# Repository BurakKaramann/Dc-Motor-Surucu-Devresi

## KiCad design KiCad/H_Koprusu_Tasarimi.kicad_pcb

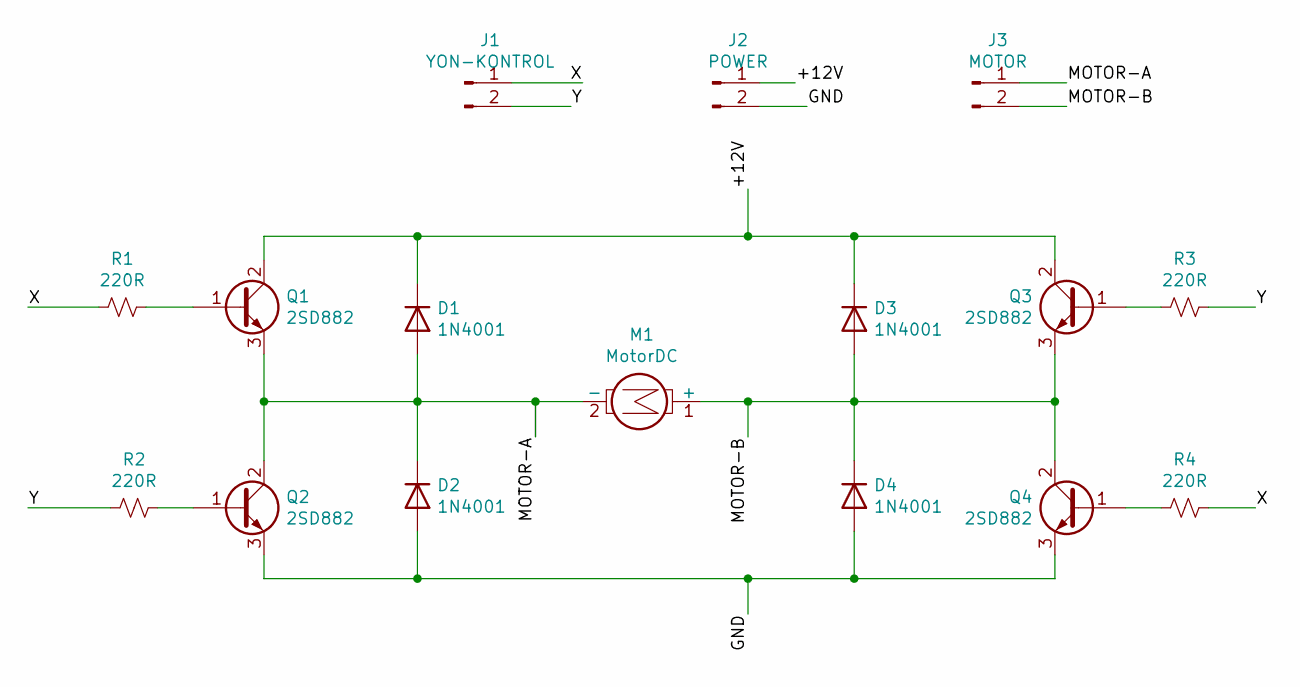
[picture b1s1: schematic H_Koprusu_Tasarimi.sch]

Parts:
D1, D2, D3, D4: 1N4001; D_DO-41_SOD81_P10.16mm_Horizontal
J1: YON-KONTROL; TerminalBlock_4Ucon_1x02_P3.50mm_Horizontal
J2: POWER; TerminalBlock_4Ucon_1x02_P3.50mm_Horizontal
J3: MOTOR; TerminalBlock_4Ucon_1x02_P3.50mm_Horizontal
M1: MotorDC
Q1, Q2, Q3, Q4: 2SD882; TO-126-3_Vertical
R1, R2, R3, R4: 220R; R_Axial_DIN0207_L6.3mm_D2.5mm_P7.62mm_Horizontal

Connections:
/+12V: D1.1 (K), D3.1 (K), J2.1, Q1.2 (C), Q3.2 (C)
/GND: D2.2 (A), D4.2 (A), J2.2, Q2.3 (E), Q4.3 (E)
/MOTOR-A: D1.2 (A), D2.1 (K), J3.1, M1.2 (-), Q1.3 (E), Q2.2 (C)
/MOTOR-B: D3.2 (A), D4.1 (K), J3.2, M1.1 (+), Q3.3 (E), Q4.2 (C)
/X: J1.1, R1.2, R4.1
/Y: J1.2, R2.2, R3.1
unnamed: Q1.1 (B), R1.1
unnamed: Q2.1 (B), R2.1
unnamed: Q3.1 (B), R3.2
unnamed: Q4.1 (B), R4.2

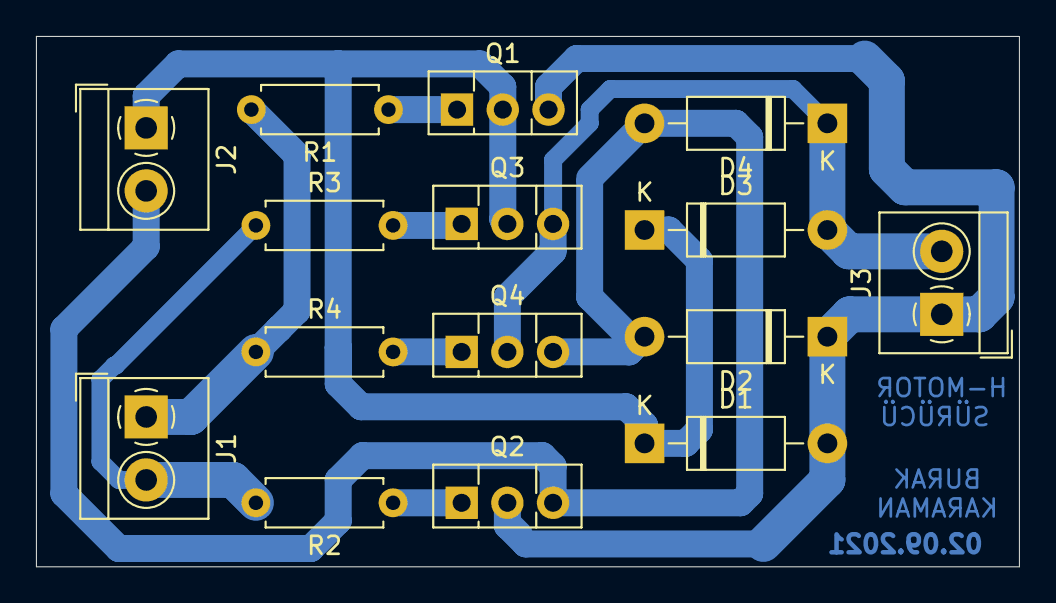
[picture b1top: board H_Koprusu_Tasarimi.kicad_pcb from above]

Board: 2 copper layers, 54.6 x 29.5 mm, 15 parts (0 on the bottom side), 10 nets.

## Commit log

2021-09-05 Dc motor surucu devresi tasarımı
    youtube için
